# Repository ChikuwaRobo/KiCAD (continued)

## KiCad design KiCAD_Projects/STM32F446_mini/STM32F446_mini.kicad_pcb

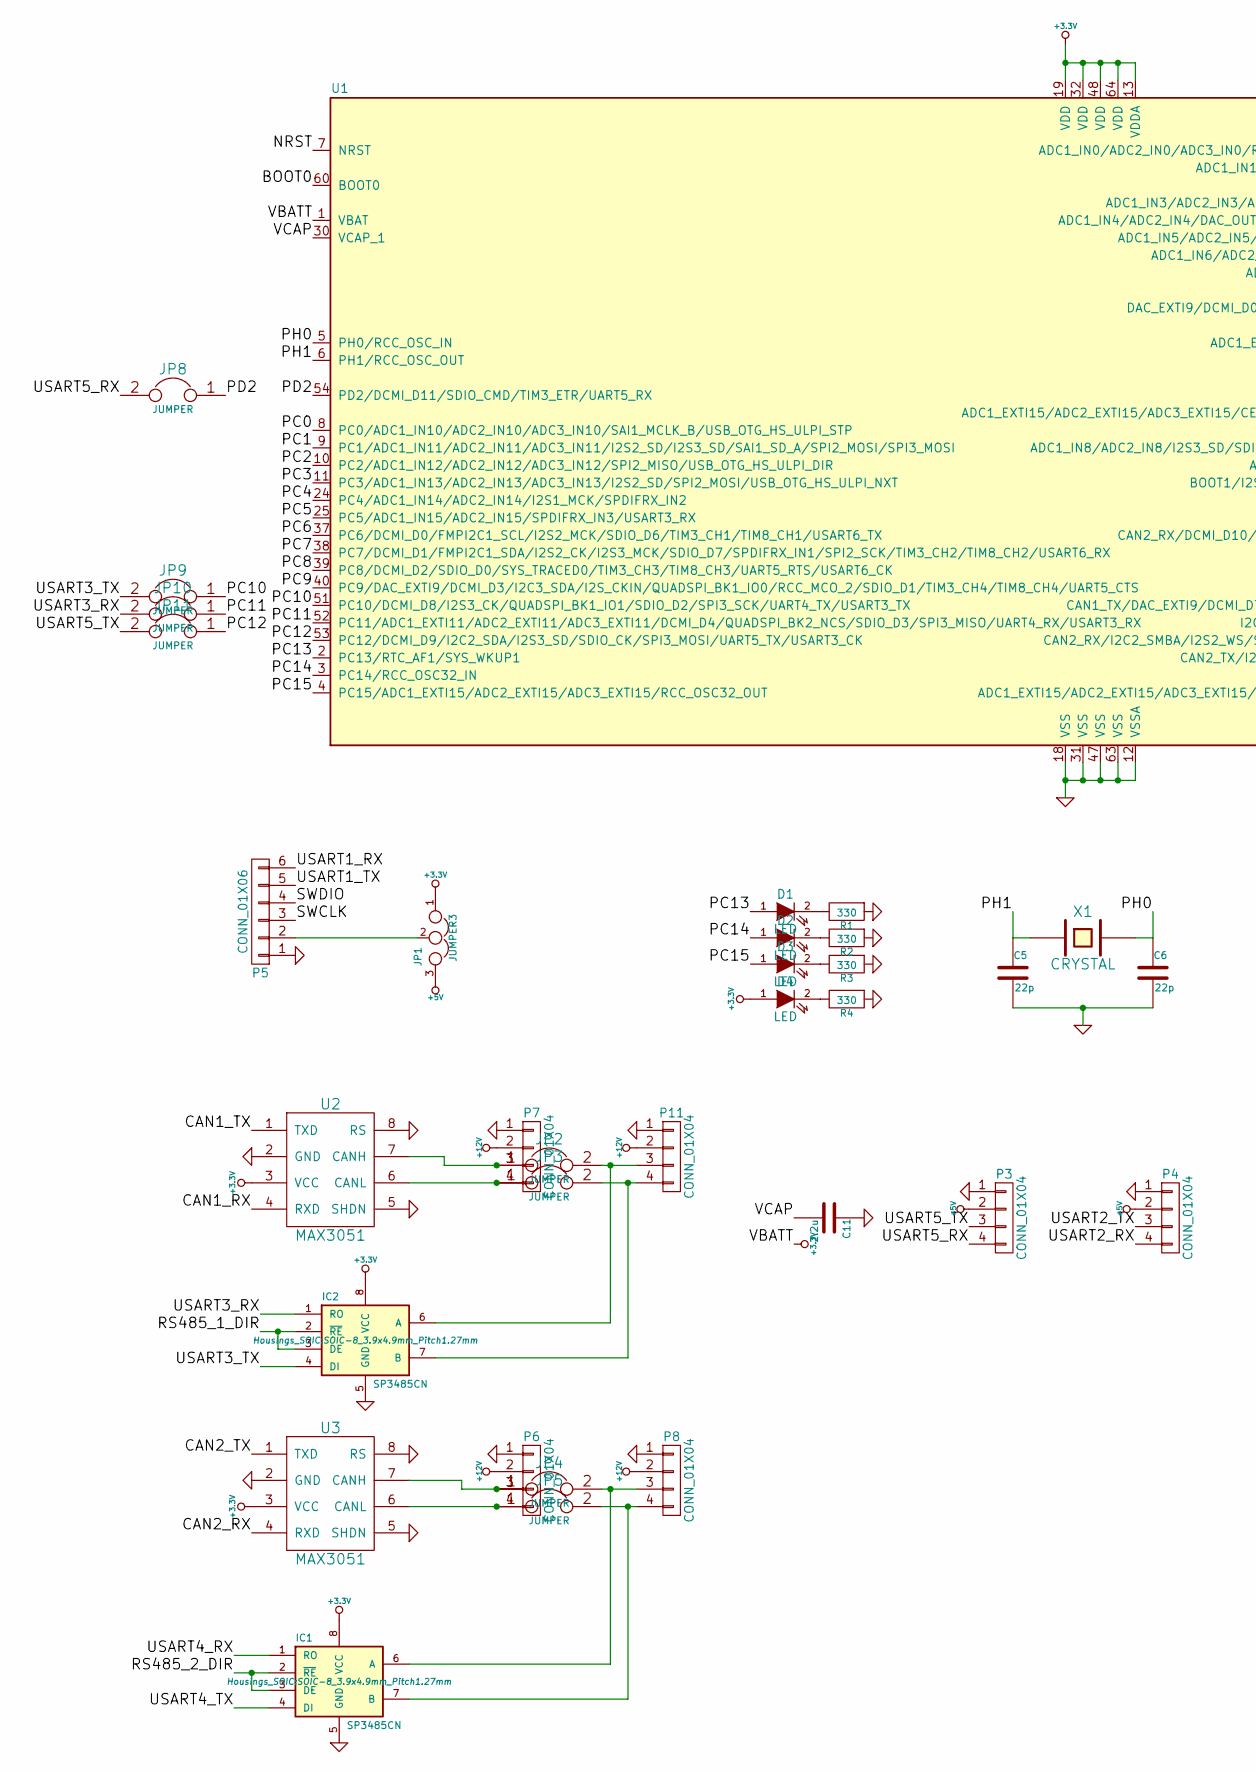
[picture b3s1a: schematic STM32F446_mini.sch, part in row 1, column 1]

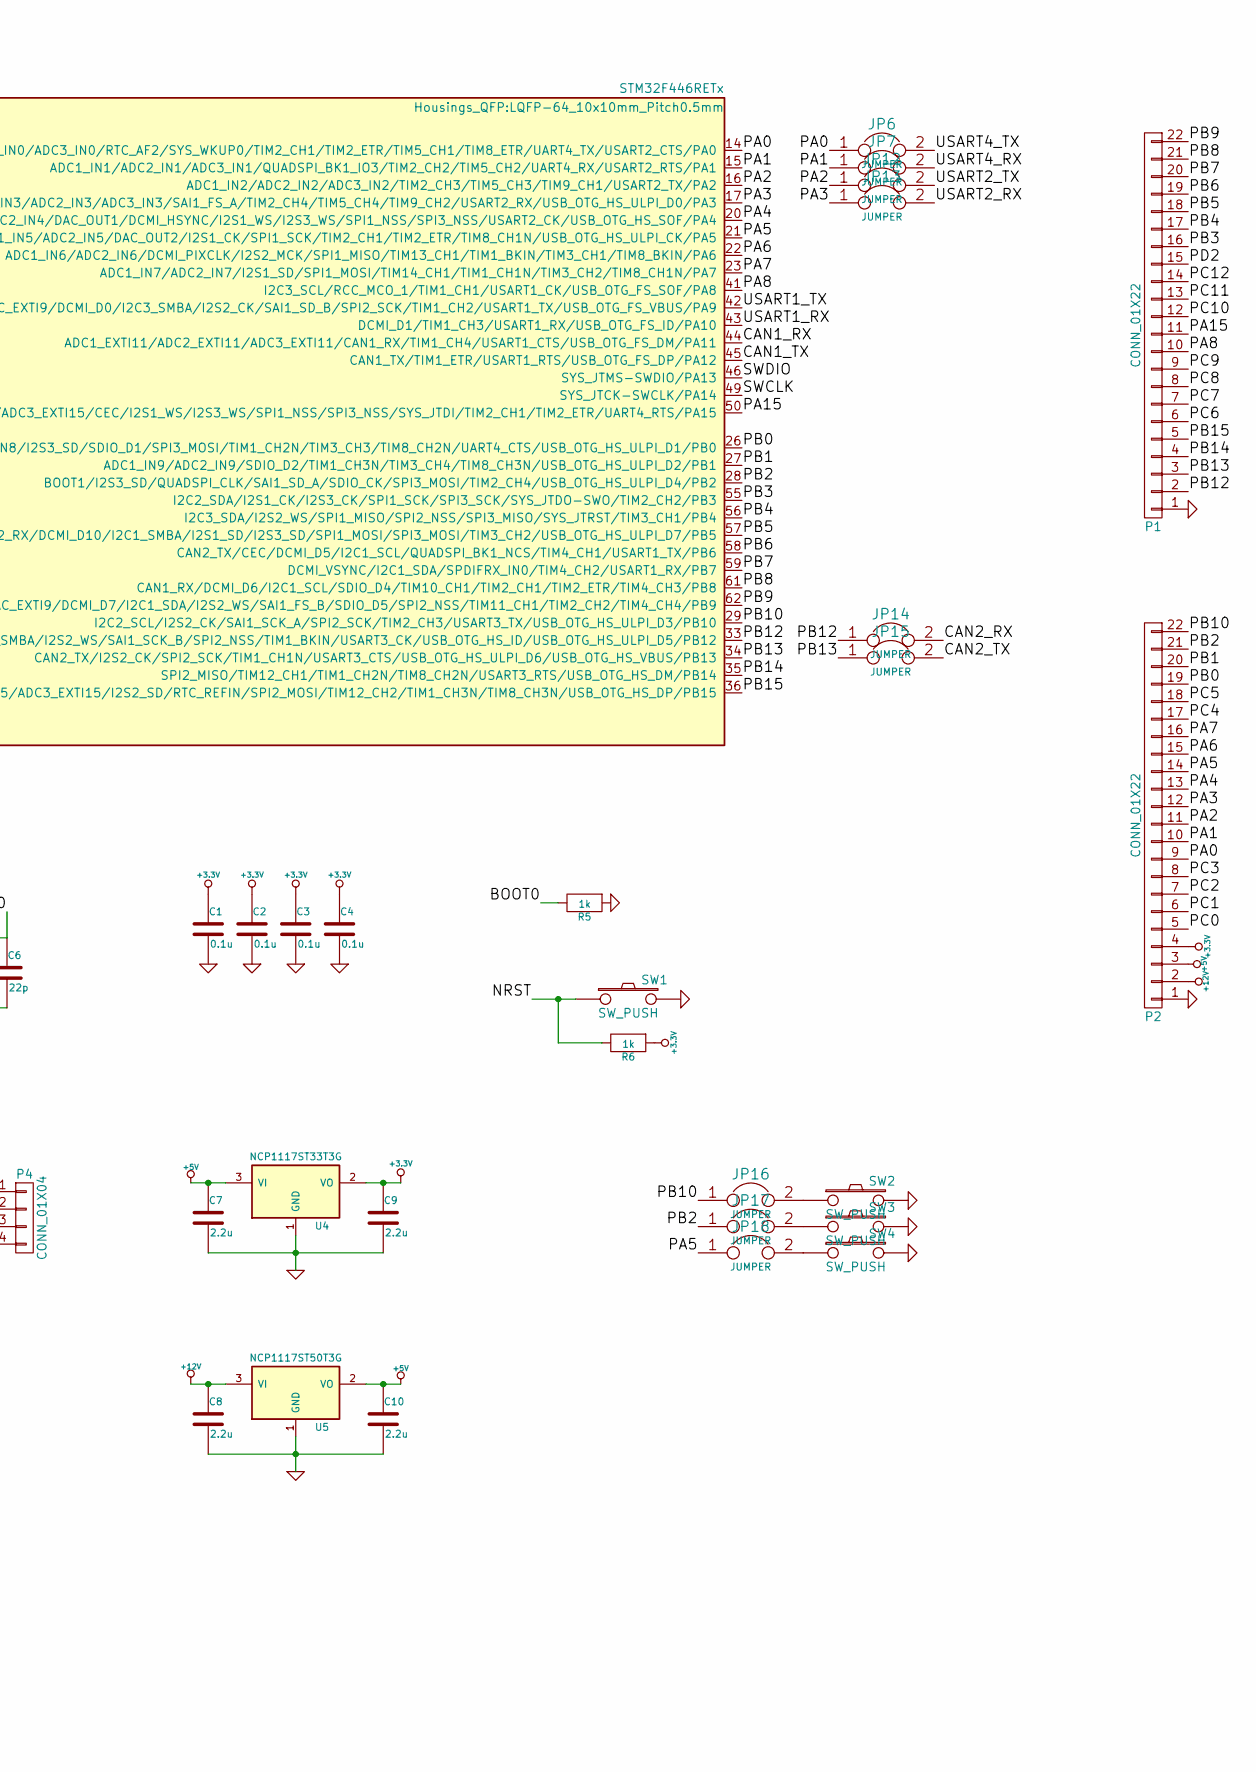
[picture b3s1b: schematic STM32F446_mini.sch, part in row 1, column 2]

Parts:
C1, C2, C3, C4: 0.1u; C1608_WP
C5, C6: 22p; C1608_WP
C7, C8, C9, C10, C11: 2.2u; C3216
D1, D2, D3, D4: LED; LED_0603
IC1, IC2: SP3485CN; SOIC-8_3.9x4.9mm_Pitch1.27mm
JP1: JUMPER3; GS3
JP2, JP3, JP4, JP5, JP6, JP7, JP8, JP9, JP10, JP11, JP12, JP13, JP14, JP15, JP16, JP17, JP18: JUMPER; GS2
P1, P2: CONN_01X22; Pin_Header_Straight_1x22
P3, P4, P8, P11: CONN_01X04; XA_4T
P5: CONN_01X06; ZH_6T
P6, P7: CONN_01X04; XA_4LC
R1, R2, R3, R4: 330; C1608_WP
R5, R6: 1k; C1608_WP
SW1, SW2, SW3, SW4: SW_PUSH; RP_SMD_Button
U1: STM32F446RETx; LQFP-64_10x10mm_Pitch0.5mm
U2, U3: MAX3051; SOIC-8_3.9x4.9mm_Pitch1.27mm
U4: NCP1117ST33T3G; SOT-223_reg
U5: NCP1117ST50T3G; SOT-223_reg
X1: CRYSTAL; ABM3_2pads

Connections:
+3.3V: C1.1, C2.1, C3.1, C4.1, C9.1, D4.1 (A), IC1.8 (VCC), IC2.8 (VCC), JP1.1, P2.4, R6.1, U1.1 (VBAT), U1.13 (VDDA), U1.19 (VDD), U1.32 (VDD), U1.48 (VDD), U1.64 (VDD), U2.3 (VCC), U3.3 (VCC), U4.2 (VO)
+5V: C7.1, C10.1, JP1.3, P2.3, P3.2, P4.2, U4.3 (VI), U5.2 (VO)
+12V: C8.1, P2.2, P6.2, P7.2, P8.2, P11.2, U5.3 (VI)
/BOOT0: R5.2, U1.60 (BOOT0)
/CAN1_RX: U1.44 (ADC1_EXTI11/ADC2_EXTI11/ADC3_EXTI11/CAN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), U2.4 (RXD)
/CAN1_TX: U1.45 (CAN1_TX/TIM1_ETR/USART1_RTS/USB_OTG_FS_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), U2.1 (TXD)
/CAN2_RX: JP14.2, U3.4 (RXD)
/CAN2_TX: JP15.2, U3.1 (TXD)
/NRST: R6.2, SW1.1, U1.7 (NRST)
/PA0: JP6.1, P2.9, U1.14 (ADC1_IN0/ADC2_IN0/ADC3_IN0/RTC_AF2/SYS_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)
/PA1: JP7.1, P2.10, U1.15 (ADC1_IN1/ADC2_IN1/ADC3_IN1/QUADSPI_BK1_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)
/PA2: JP12.1, P2.11, U1.16 (ADC1_IN2/ADC2_IN2/ADC3_IN2/TIM2_CH3/TIM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)
/PA3: JP13.1, P2.12, U1.17 (ADC1_IN3/ADC2_IN3/ADC3_IN3/SAI1_FS_A/TI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)
/PA4: P2.13, U1.20 (ADC1_IN4/ADC2_IN4/DAC_OUT1/DCMI_HSYNC/I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)
/PA5: JP18.1, P2.14, U1.21 (ADC1_IN5/ADC2_IN5/DAC_OUT2/I2S1_CK/SPI1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)
/PA6: P2.15, U1.22 (ADC1_IN6/ADC2_IN6/DCMI_PIXCLK/I2S2_MCK/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)
/PA7: P2.16, U1.23 (ADC1_IN7/ADC2_IN7/I2S1_SD/SPI1_MOSI/TIM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)
/PA8: P1.10, U1.41 (I2C3_SCL/RCC_MCO_1/TIM1_CH1/USART1_CK/U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)
/PA15: P1.11, U1.50 (ADC1_EXTI15/ADC2_EXTI15/ADC3_EXTI15/CEC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)
/PB0: P2.19, U1.26 (ADC1_IN8/ADC2_IN8/I2S3_SD/SDIO_D1/SPI3_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)
/PB1: P2.20, U1.27 (ADC1_IN9/ADC2_IN9/SDIO_D2/TIM1_CH3N/TIM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)
/PB2: JP17.1, P2.21, U1.28 (BOOT1/I2S3_SD/QUADSPI_CLK/SAI1_SD_A/SDI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)
/PB3: P1.16, U1.55 (I2C2_SDA/I2S1_CK/I2S3_CK/SPI1_SCK/SPI3_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)
/PB4: P1.17, U1.56 (I2C3_SDA/I2S2_WS/SPI1_MISO/SPI2_NSS/SPI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)
/PB5: P1.18, U1.57 (CAN2_RX/DCMI_D10/I2C1_SMBA/I2S1_SD/I2S3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)
/PB6: P1.19, U1.58 (CAN2_TX/CEC/DCMI_D5/I2C1_SCL/QUADSPI_BK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)
/PB7: P1.20, U1.59 (DCMI_VSYNC/I2C1_SDA/SPDIFRX_IN0/TIM4_CH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)
/PB8: P1.21, U1.61 (CAN1_RX/DCMI_D6/I2C1_SCL/SDIO_D4/TIM10_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)
/PB9: P1.22, U1.62 (CAN1_TX/DAC_EXTI9/DCMI_D7/I2C1_SDA/I2S2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)
/PB10: JP16.1, P2.22, U1.29 (I2C2_SCL/I2S2_CK/SAI1_SCK_A/SPI2_SCK/TI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)
/PB12: JP14.1, P1.2, U1.33 (CAN2_RX/I2C2_SMBA/I2S2_WS/SAI1_SCK_B/SP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)
/PB13: JP15.1, P1.3, U1.34 (CAN2_TX/I2S2_CK/SPI2_SCK/TIM1_CH1N/USAR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)
/PB14: P1.4, U1.35 (SPI2_MISO/TIM12_CH1/TIM1_CH2N/TIM8_CH2N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)
/PB15: P1.5, U1.36 (ADC1_EXTI15/ADC2_EXTI15/ADC3_EXTI15/I2S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)
/PC0: P2.5, U1.8 (PC0/ADC1_IN10/ADC2_IN10/ADC3_IN10/SAI1_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)
/PC1: P2.6, U1.9 (PC1/ADC1_IN11/ADC2_IN11/ADC3_IN11/I2S2_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)
/PC2: P2.7, U1.10 (PC2/ADC1_IN12/ADC2_IN12/ADC3_IN12/SPI2_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)
/PC3: P2.8, U1.11 (PC3/ADC1_IN13/ADC2_IN13/ADC3_IN13/I2S2_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)
/PC4: P2.17, U1.24 (PC4/ADC1_IN14/ADC2_IN14/I2S1_MCK/SPDIFR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)
/PC5: P2.18, U1.25 (PC5/ADC1_IN15/ADC2_IN15/SPDIFRX_IN3/USA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)
/PC6: P1.6, U1.37 (PC6/DCMI_D0/FMPI2C1_SCL/I2S2_MCK/SDIO_D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)
/PC7: P1.7, U1.38 (PC7/DCMI_D1/FMPI2C1_SDA/I2S2_CK/I2S3_MC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)
/PC8: P1.8, U1.39 (PC8/DCMI_D2/SDIO_D0/SYS_TRACED0/TIM3_CH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)
/PC9: P1.9, U1.40 (PC9/DAC_EXTI9/DCMI_D3/I2C3_SDA/I2S_CKIN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)
/PC10: JP9.1, P1.12, U1.51 (PC10/DCMI_D8/I2S3_CK/QUADSPI_BK1_IO1/SD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)
/PC11: JP10.1, P1.13, U1.52 (PC11/ADC1_EXTI11/ADC2_EXTI11/ADC3_EXTI1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)
/PC12: JP11.1, P1.14, U1.53 (PC12/DCMI_D9/I2C2_SDA/I2S3_SD/SDIO_CK/S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)
/PC13: D1.1 (A), U1.2 (PC13/RTC_AF1/SYS_WKUP1)
/PC14: D2.1 (A), U1.3 (PC14/RCC_OSC32_IN)
/PC15: D3.1 (A), U1.4 (PC15/ADC1_EXTI15/ADC2_EXTI15/ADC3_EXTI1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)
/PD2: JP8.1, P1.15, U1.54 (PD2/DCMI_D11/SDIO_CMD/TIM3_ETR/UART5_RX)
/PH0: C6.1, U1.5 (PH0/RCC_OSC_IN), X1.2
/PH1: C5.1, U1.6 (PH1/RCC_OSC_OUT), X1.1
/RS485_1_DIR: IC2.2 (~RE~), IC2.3 (DE)
/RS485_2_DIR: IC1.2 (~RE~), IC1.3 (DE)
/SWCLK: P5.3, U1.49 (SYS_JTCK-SWCLK/PA14)
/SWDIO: P5.4, U1.46 (SYS_JTMS-SWDIO/PA13)
/USART1_RX: P5.6, U1.43 (DCMI_D1/TIM1_CH3/USART1_RX/USB_OTG_FS_I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)
/USART1_TX: P5.5, U1.42 (DAC_EXTI9/DCMI_D0/I2C3_SMBA/I2S2_CK/SAI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)
/USART2_RX: JP13.2, P4.4
/USART2_TX: JP12.2, P4.3
/USART3_RX: IC2.1 (RO), JP10.2
/USART3_TX: IC2.4 (DI), JP9.2
/USART4_RX: IC1.1 (RO), JP7.2
/USART4_TX: IC1.4 (DI), JP6.2
/USART5_RX: JP8.2, P3.4
/USART5_TX: JP11.2, P3.3
/VCAP: C11.2, U1.30 (VCAP_1)
GND: C1.2, C2.2, C3.2, C4.2, C5.2, C6.2, C7.2, C8.2, C9.2, C10.2, C11.1, IC1.5 (GND), IC2.5 (GND), P1.1, P2.1, P3.1, P4.1, P5.1, P6.1, P7.1, P8.1, P11.1, R1.1, R2.1, R3.1, R4.1, R5.1, SW1.2, SW2.2, SW3.2, SW4.2, U1.12 (VSSA), U1.18 (VSS), U1.31 (VSS), U1.47 (VSS), U1.63 (VSS), U2.2 (GND), U2.5 (SHDN), U2.8 (RS), U3.2 (GND), U3.5 (SHDN), U3.8 (RS), U4.1 (GND), U5.1 (GND)
unnamed: D1.2 (K), R1.2
unnamed: D2.2 (K), R2.2
unnamed: D3.2 (K), R3.2
unnamed: D4.2 (K), R4.2
unnamed: IC1.6 (A), JP4.2, P8.3
unnamed: IC1.7 (B), JP5.2, P8.4
unnamed: IC2.6 (A), JP2.2, P11.3
unnamed: IC2.7 (B), JP3.2, P11.4
unnamed: JP1.2, P5.2
unnamed: JP2.1, P7.3, U2.7 (CANH)
unnamed: JP3.1, P7.4, U2.6 (CANL)
unnamed: JP4.1, P6.3, U3.7 (CANH)
unnamed: JP5.1, P6.4, U3.6 (CANL)
unnamed: JP16.2, SW2.1
unnamed: JP17.2, SW3.1
unnamed: JP18.2, SW4.1

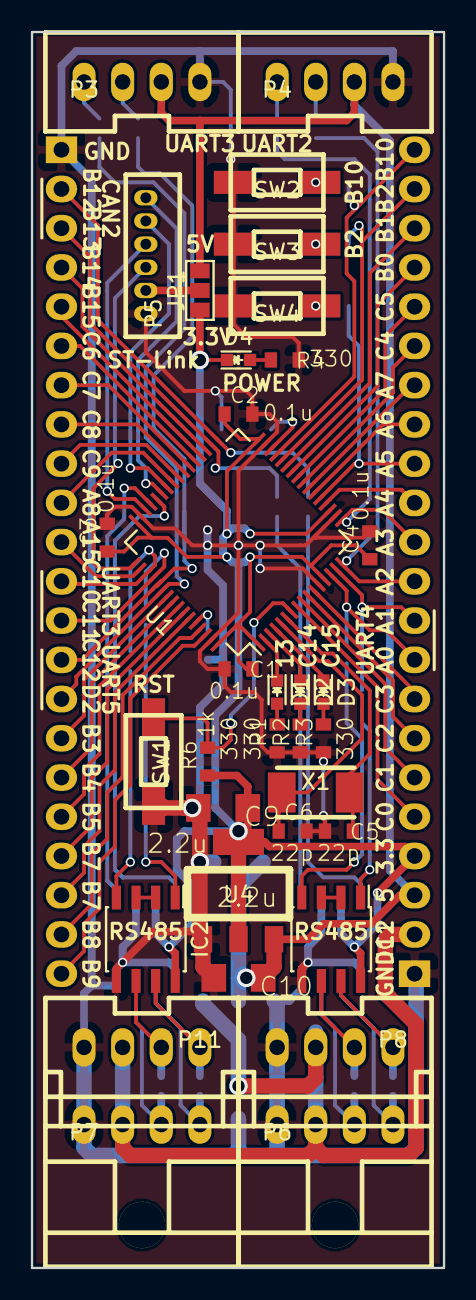
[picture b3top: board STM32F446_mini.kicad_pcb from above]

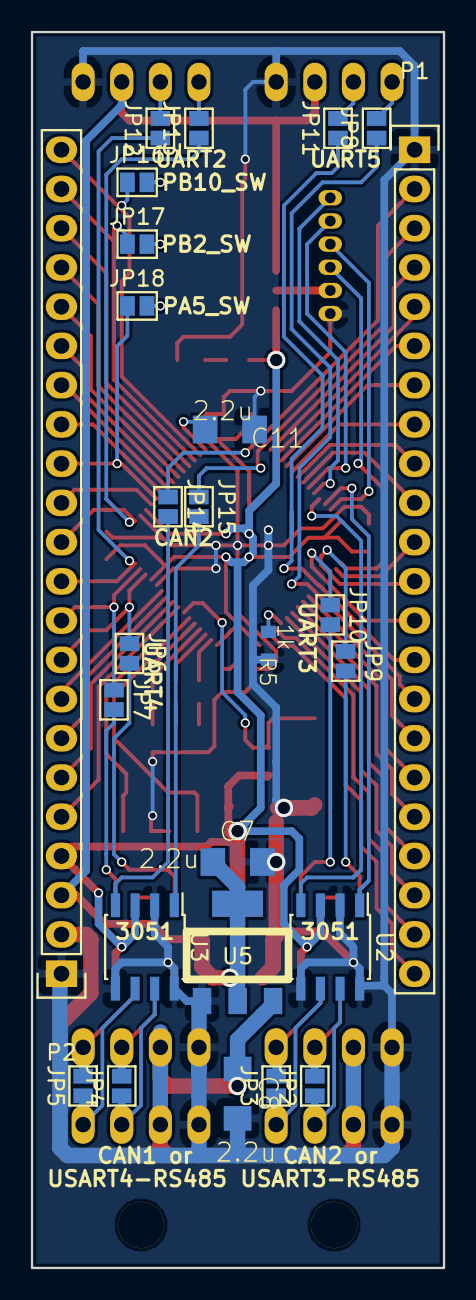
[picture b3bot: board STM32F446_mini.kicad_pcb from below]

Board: 2 copper layers, 26.7 x 80.0 mm, 60 parts (26 on the bottom side), 85 nets.

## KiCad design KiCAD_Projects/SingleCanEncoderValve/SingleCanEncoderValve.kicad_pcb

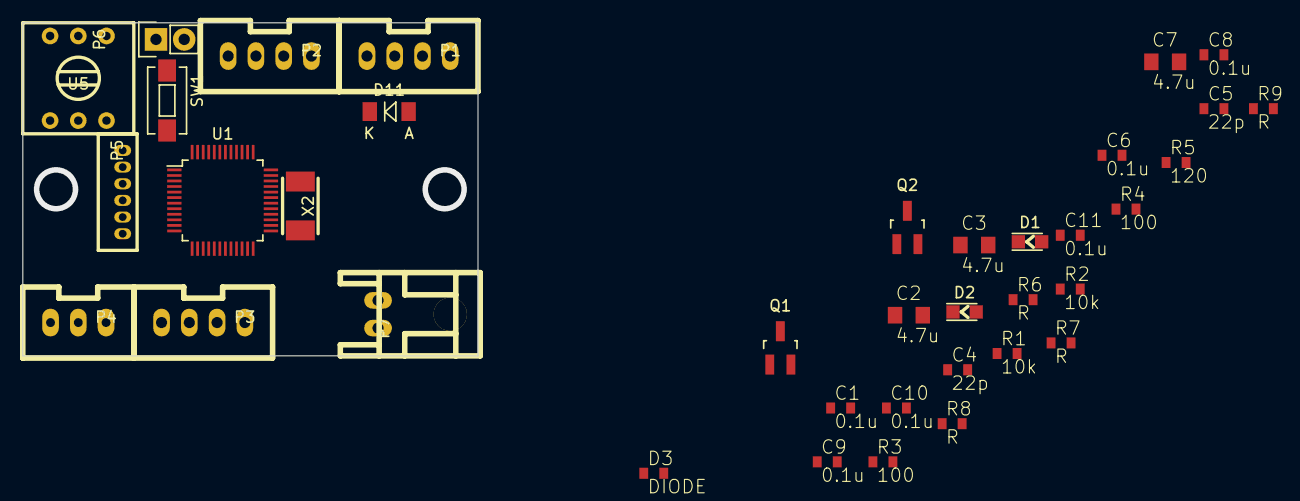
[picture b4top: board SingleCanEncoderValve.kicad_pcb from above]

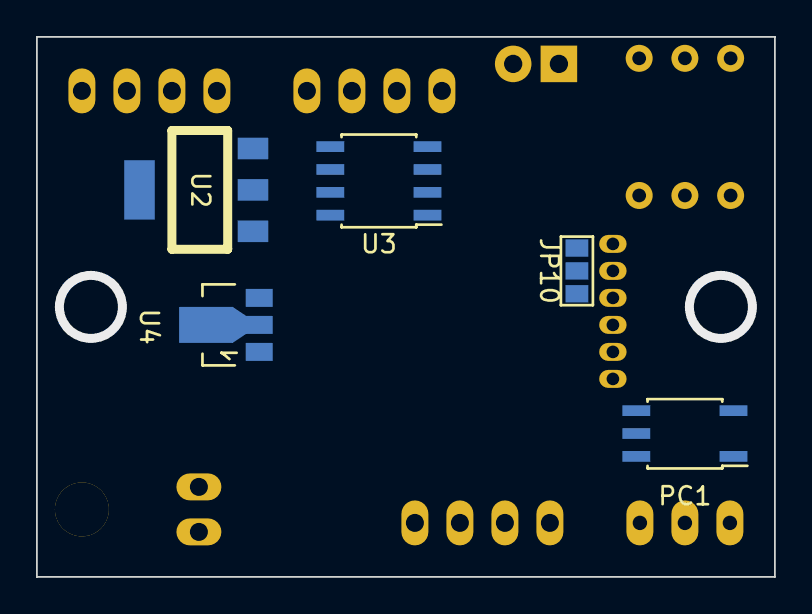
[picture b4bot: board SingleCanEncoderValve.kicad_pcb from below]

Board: 2 copper layers, 41.0 x 30.0 mm, 42 parts (5 on the bottom side), 37 nets, no tracks yet.

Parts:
C1, C6, C8, C9, C10, C11: 0.1u; C1608_WP
C2, C3, C7: 4.7u; C2012
C4, C5: 22p; C1608_WP
D1, D2: LED; LED_0805
D3: DIODE; C1608_WP
D11: DIODE; MiniMELF_Standard
JP10: JUMPER3; GS3
P1, P2, P3: CONN_01X04; XA_4T
P4: CONN_01X03; XA_3T
P5: CONN_01X06; ZH_6T
P6: CONN_01X02; Pin_Header_Straight_1x02
P7: CONN_01X02; XA_2LC
PC1: TLP117; SOIC-5_3.9x4.9mm_Pitch1.27mm
Q1, Q2: MOSFET_N; SOT-23_Handsoldering
R1, R2: 10k; C1608_WP
R3, R4: 100; C1608_WP
R5: 120; C1608_WP
R6, R7, R8, R9: R; C1608_WP
SW1: SW_PUSH; SW_SPST_EVQPE1
U1: STM32F103_48; LQFP-48_7x7mm_Pitch0.5mm
U2: NCP1117ST33T3G; SOT-223_reg
U3: MAX3051; SOIC-8_3.9x4.9mm_Pitch1.27mm
U4: SOT-89-3regul; SOT89-3_Housing
U5: SW_ROTARY_16; rotary_0F
X2: CRYSTAL; ABM3_2pads

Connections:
+3.3V: C3.1, C6.2, C8.2, C9.2, C10.2, C11.2, D1.1, JP10.3, R1.1, R6.1, R7.1, U1.1, U1.9, U1.24, U1.36, U1.48, U3.3, U4.1
+5V: C7.1, P3.2, PC1.1, U2.2, U4.3
+12V: C2.1, D3.1, D11.1, P7.1, U2.3
/BOOT0: R2.2, U1.44
/CAN_H: P1.3, P2.3, P6.1, U3.7
/CAN_L: P1.4, P2.4, R5.1, U3.6
/CAN_RX: U1.32, U3.4
/CAN_TX: U1.33, U3.1
/ENC_A: P3.3, R6.2, U1.10
/ENC_B: P3.4, R7.2, U1.11
/LED: D2.1, U1.18
/NRST: C1.2, JP10.1, R1.2, SW1.2, U1.7
/OSC_IN: C4.1, U1.5, X2.1
/OSC_OUT: C5.1, U1.6, X2.2
/PWM_A: Q1.G, U1.14
/SEL_1: U1.2, U5.1
/SEL_2: U1.3, U5.3
/SEL_4: U1.4, U5.4
/SEL_8: U1.12, U5.6
/SWCLK: P5.3, U1.37
/SWDIO: P5.4, U1.34
/USART_RX: P5.6, U1.31
/USART_TX: P5.5, U1.30
/VALVE: R9.2, U1.17
GND: C1.1, C2.2, C3.2, C4.2, C5.2, C6.1, C7.2, C8.1, C9.1, C10.1, C11.1, P1.1, P2.1, P3.1, P5.1, Q1.S, Q2.S, R2.1, R3.2, R4.2, SW1.1, U1.8, U1.23, U1.35, U1.47, U2.1, U3.2, U3.5, U3.8, U4.2, U5.2, U5.5
unnamed: D1.2, R3.1
unnamed: D2.2, R4.1
unnamed: D3.2, P7.2, Q2.D
unnamed: D11.2, P1.2, P2.2
unnamed: JP10.2, P5.2
unnamed: P4.1, PC1.4
unnamed: P4.2, PC1.6
unnamed: P4.3, PC1.5
unnamed: P6.2, R5.2
unnamed: PC1.3, R8.1
unnamed: Q1.D, R8.2
unnamed: Q2.G, R9.1
